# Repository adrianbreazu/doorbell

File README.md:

# doorbell

## Schema

## Hardware
1. Arduino 168 Pro mini - [link](https://www.ebay.com/itm/Arduino-Pro-Mini-Atmega168-Module-5V-16M-/391722268803?_trksid=p2349526.m4383.l4275.c1)
2. Catalex MP3 - [link](https://www.ebay.com/itm/UART-Control-Serial-MP3-Music-Player-Module-For-Arduino-AVR-ARM-PIC-/311133945527)
3. Radio - [link](https://www.ebay.com/itm/433MHz-Radio-Transceiver-Transmitter-Sender-Module-Remote-Arduino-L2/182950258189?epid=1871566586&hash=item2a98af660d:g:Wq0AAOSwi8xaKO2M)
4. 5v power source

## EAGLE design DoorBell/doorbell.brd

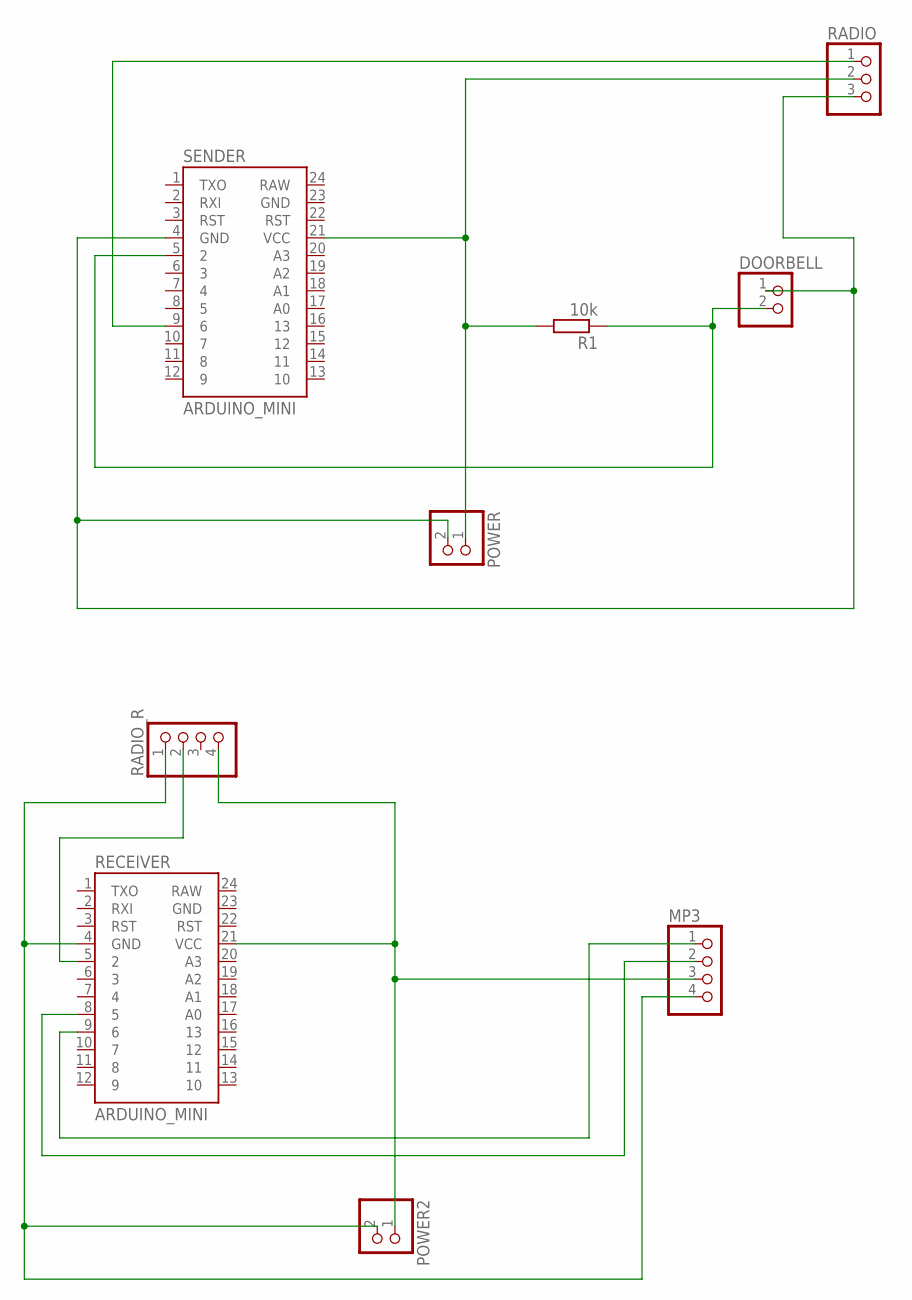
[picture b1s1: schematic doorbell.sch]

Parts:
DOORBELL: PINHD-1X2/90; 1X02/90
MP3: PINHD-1X4/90; 1X04/90
POWER, POWER2: PINHD-1X2/90; 1X02/90
R1: 10k; 0207/10
RADIO: PINHD-1X3/90; 1X03/90
RADIO_R: PINHD-1X4/90; 1X04/90
RECEIVER: ARDUINO_MINI
SENDER: ARDUINO_MINI

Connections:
5V: POWER.1, R1.2, RADIO.2, SENDER.21 (VCC)
5V_2: MP3.3, POWER2.1, RADIO_R.4, RECEIVER.21 (VCC)
5V_R: DOORBELL.2, R1.1, SENDER.5 (2)
DATA: RADIO_R.2, RECEIVER.5 (2)
GND: DOORBELL.1, POWER.2, RADIO.3, SENDER.4 (GND)
GND2: MP3.4, POWER2.2, RADIO_R.1, RECEIVER.4 (GND)
RADIO: RADIO.1, SENDER.9 (6)
RX-TX: MP3.2, RECEIVER.8 (5)
TX-RX: MP3.1, RECEIVER.9 (6)

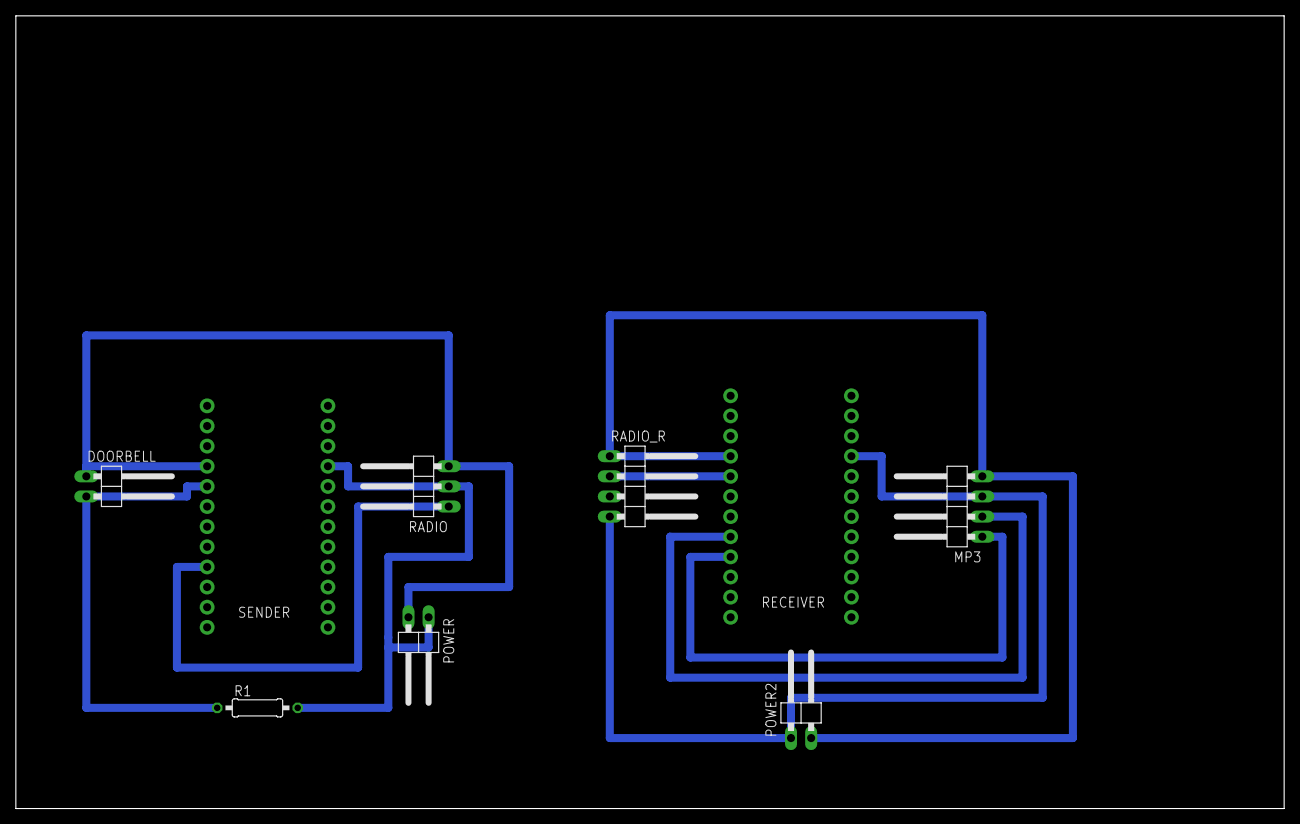
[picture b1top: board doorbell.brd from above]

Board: 2 copper layers, 160.0 x 100.0 mm, 9 parts (0 on the bottom side), 9 nets.

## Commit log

2017-12-24 arduino code
2017-12-24 add pcb design
2017-12-31 add design
2017-12-31 update design

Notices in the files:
parts and their libraries:
SparkFun-Boards: Licensing: Creative Commons ShareAlike 4.0 International - https://creativecommons.org/licenses/by-sa/4.0
